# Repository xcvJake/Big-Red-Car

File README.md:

# Big-Red-Car
Code for the JCU Big Red Car Project

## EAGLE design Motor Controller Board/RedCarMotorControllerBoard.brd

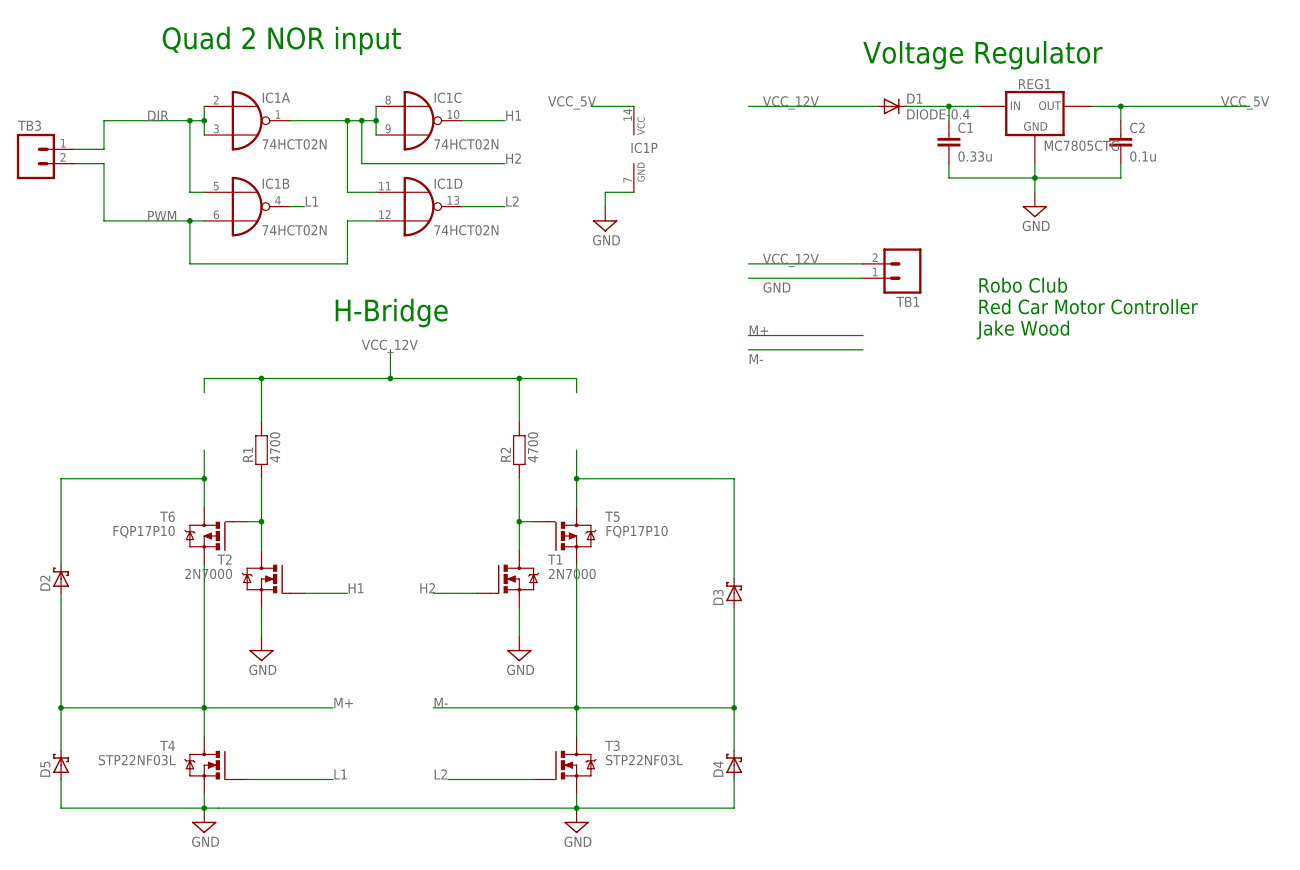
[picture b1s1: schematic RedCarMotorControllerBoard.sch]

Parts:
C1: 0.33u; RADIAL-0.2
C2: 0.1u; RADIAL-0.2
D1: DIODE-0.4
D2, D3, D4, D5: SCHOTTKY-DIODEDO201T15; DO201T15
IC1: 74HCT02N; DIL14
R1, R2: 4700; AXIAL-0.4
REG1: MC7805CTG; TO220-UPRIGHT
T1, T2: 2N7000; TO92-
T3, T4: STP22NF03L; TO220-UPRIGHT
T5, T6: FQP17P10; TO220-UPRIGHT
TB1, TB3: KK-CONNECT-2WAY_PG; KK-CONNECT-2WAY-PG

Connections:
DIR: IC1.2 (I0), IC1.3 (I1), IC1.5 (I0), TB3.1
GND: C1.P$2 (2), C2.P$2 (2), D4.A, D5.A, IC1.7 (GND), REG1.2 (GND), T1.3 (S), T2.3 (S), T3.3 (S), T4.3 (S), TB1.1
H1: IC1.10 (O), T2.2 (G)
H2: IC1.1 (O), IC1.8 (I0), IC1.9 (I1), IC1.11 (I0), T1.2 (G)
L1: IC1.4 (O), T4.1 (G)
L2: IC1.13 (O), T3.1 (G)
M+: D2.A, D5.C, T4.2 (D), T6.2 (D)
M-: D3.A, D4.C, T3.2 (D), T5.2 (D)
unnamed: C1.P$1 (1), D1.C, REG1.1 (IN)
unnamed: D3.C, T5.3 (S)
unnamed: R1.P$1 (1), T2.1 (D), T6.1 (G)
unnamed: R2.P$1 (1), T1.1 (D), T5.1 (G)
unnamed: D2.C, T6.3 (S)
PWM: IC1.6 (I1), IC1.12 (I1), TB3.2
VCC_5V: C2.P$1 (1), IC1.14 (VCC), REG1.3 (OUT)
VCC_12V: D1.A, R1.P$2 (2), R2.P$2 (2), TB1.2

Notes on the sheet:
Voltage Regulator
H-Bridge
Quad 2 NOR input
Robo Club Red Car Motor Controller Jake Wood

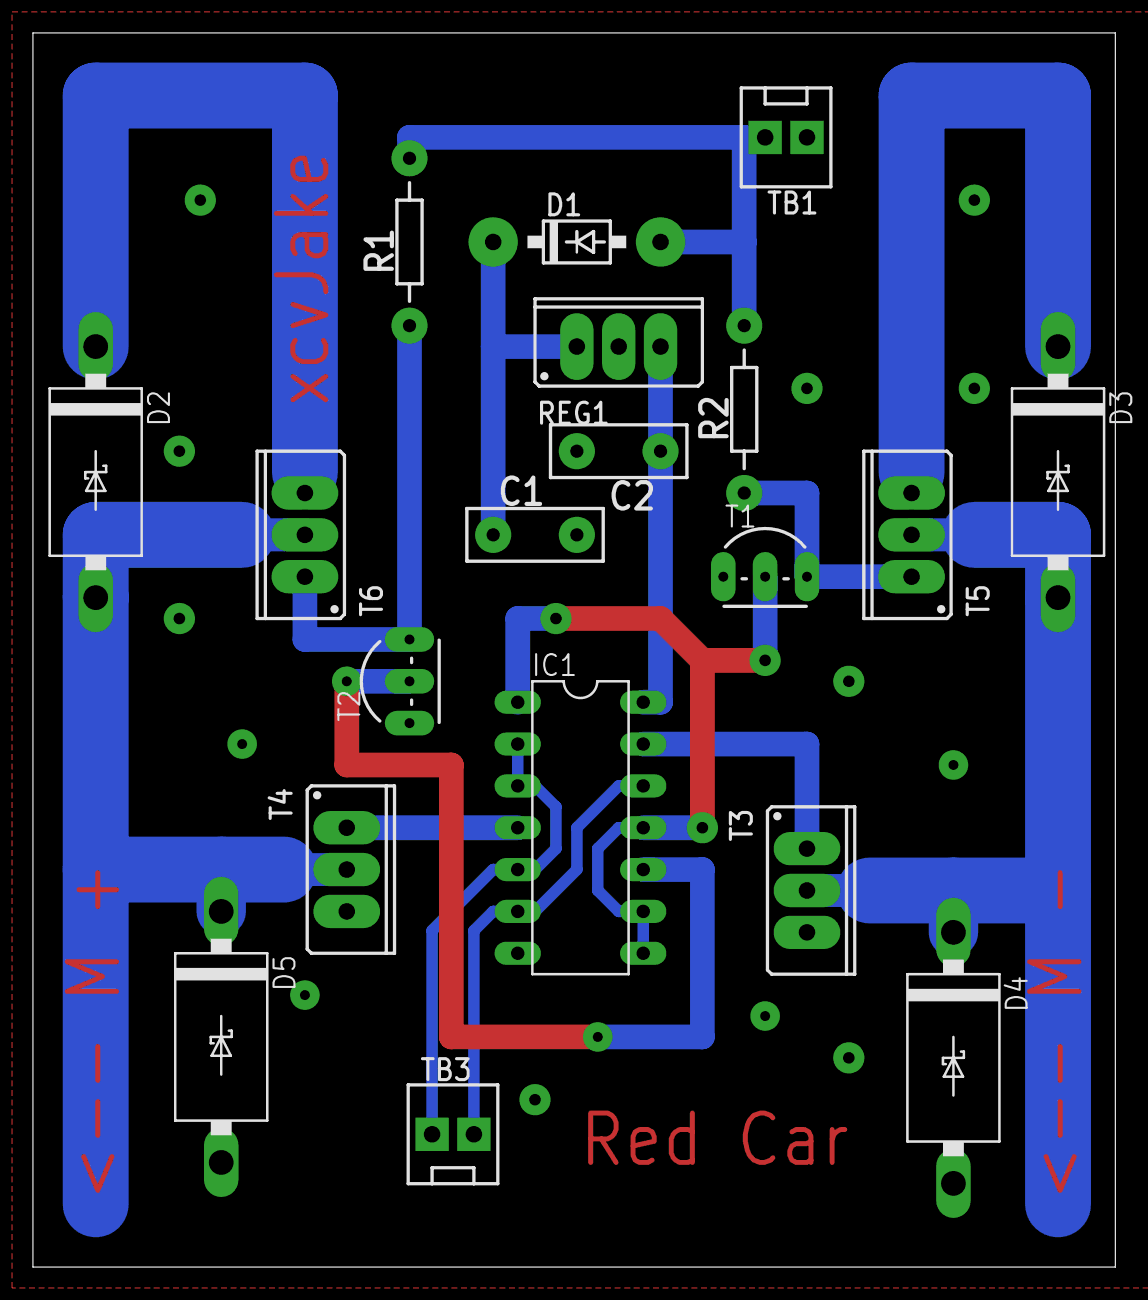
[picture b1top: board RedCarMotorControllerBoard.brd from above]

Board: 2 copper layers, 65.7 x 74.9 mm, 19 parts (0 on the bottom side), 16 nets.

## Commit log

2015-07-24 The working code for the Big Red Car
2015-07-29 Changed the frequency of the PWM, didnt really help because the closest frequency to 20kHz is 7kHz.
